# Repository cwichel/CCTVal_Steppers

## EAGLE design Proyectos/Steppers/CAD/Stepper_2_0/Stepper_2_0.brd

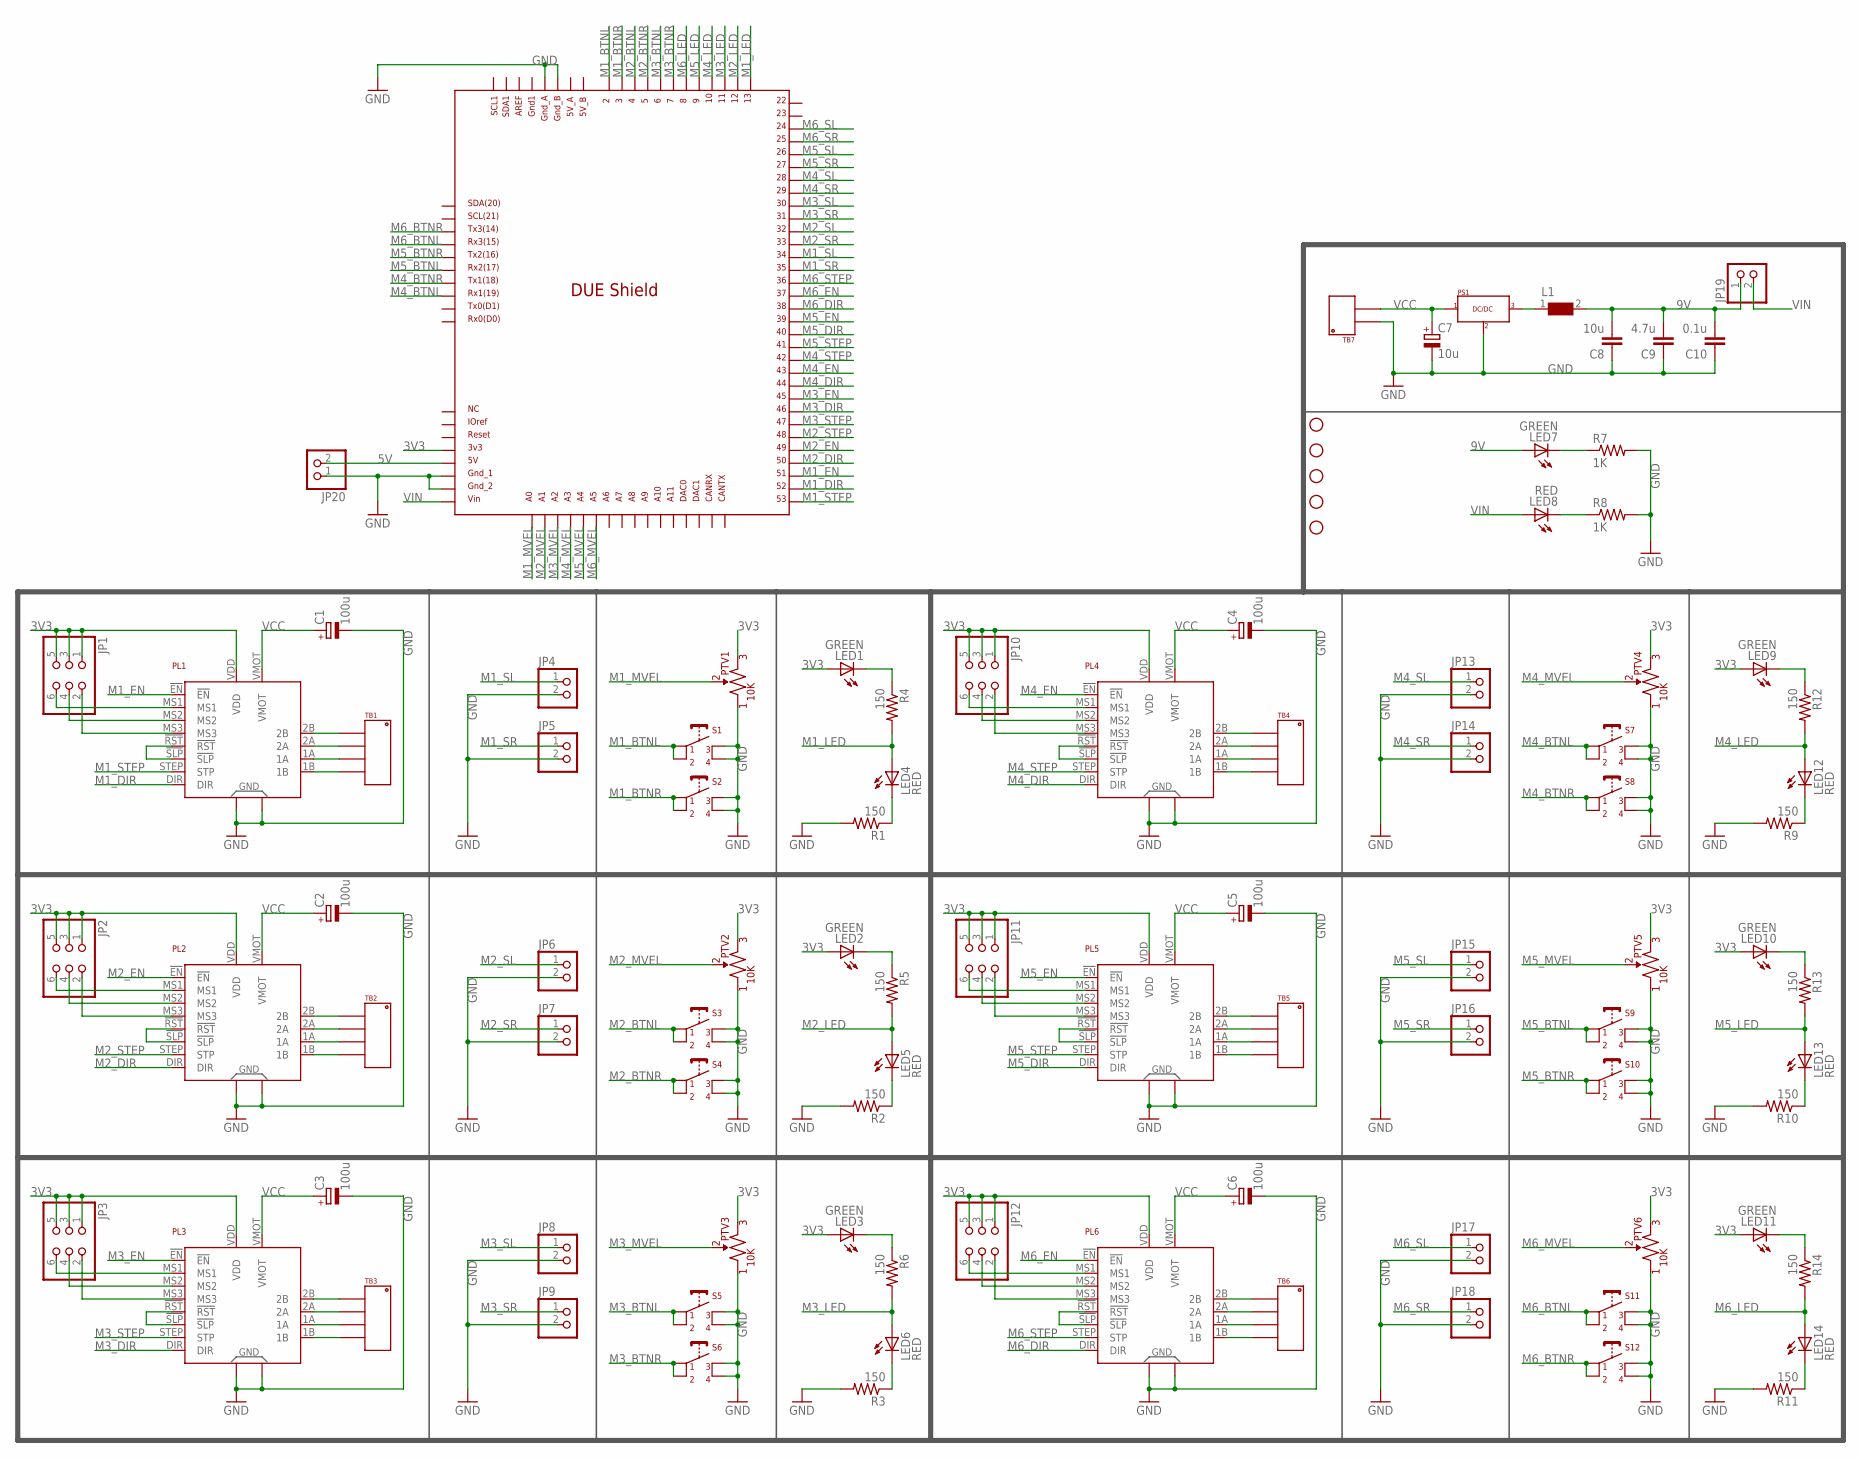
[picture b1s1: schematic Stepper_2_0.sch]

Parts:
C1, C2, C3, C4, C5, C6: 100u; ETR2
C7: 10u; E2-4
C8: 10u; 1206
C9: 4.7u; 1206
C10: 0.1u; 1206
DUE1: DUE(NOSPI)
H1, H2, H3, H4, H5: STAND-OFF
JP1, JP2, JP3, JP10, JP11, JP12: PINHD-2X3; 2X03
JP4, JP5, JP6, JP7, JP8, JP9, JP13, JP14, JP15, JP16, JP17, JP18, JP19, JP20: PINHD-1X2; 1X02
L1: WE-CBF-742792118_1206; 1206
LED1, LED2, LED3, LED7, LED9, LED10, LED11: GREEN; 1206
LED4, LED5, LED6, LED8, LED12, LED13, LED14: RED; 1206
PL1, PL2, PL3, PL4, PL5, PL6: A4988X; MD09X
PS1: VX78-500
PTV1, PTV2, PTV3, PTV4, PTV5, PTV6: 10K; PTV09A-4
R1, R2, R3, R4, R5, R6, R9, R10, R11, R12, R13, R14: 150; 1206
R7, R8: 1K; 1206
S1, S2, S3, S4, S5, S6, S7, S8, S9, S10, S11, S12: BTN_SPST_6MM
TB1, TB2, TB3, TB4, TB5, TB6: TB_HEAD_3.5MM_01X04
TB7: TB_HEAD_3.5MM_01X02

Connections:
3V3: DUE1.3V3, JP1.1, JP1.3, JP1.5, JP2.1, JP2.3, JP2.5, JP3.1, JP3.3, JP3.5, JP10.1, JP10.3, JP10.5, JP11.1, JP11.3, JP11.5, JP12.1, JP12.3, JP12.5, LED1.A, LED2.A, LED3.A, LED9.A, LED10.A, LED11.A, PL1.VDD, PL2.VDD, PL3.VDD, PL4.VDD, PL5.VDD, PL6.VDD, PTV1.P$3 (3), PTV2.P$3 (3), PTV3.P$3 (3), PTV4.P$3 (3), PTV5.P$3 (3), PTV6.P$3 (3)
5V: DUE1.5V, JP20.2
9V: C8.2, C9.2, C10.2, JP19.1, L1.2, LED7.A
GND: C1.-, C2.-, C3.-, C4.-, C5.-, C6.-, C7.-, C8.1, C9.1, C10.1, DUE1.GND_1, DUE1.GND_2, DUE1.GND_A, DUE1.GND_B, JP4.2, JP5.2, JP6.2, JP7.2, JP8.2, JP9.2, JP13.2, JP14.2, JP15.2, JP16.2, JP17.2, JP18.2, JP20.1, PL1.GND1, PL1.GND2, PL2.GND1, PL2.GND2, PL3.GND1, PL3.GND2, PL4.GND1, PL4.GND2, PL5.GND1, PL5.GND2, PL6.GND1, PL6.GND2, PS1.P$3, PTV1.P$1 (1), PTV2.P$1 (1), PTV3.P$1 (1), PTV4.P$1 (1), PTV5.P$1 (1), PTV6.P$1 (1), R1.2, R2.2, R3.2, R7.2, R8.2, R9.2, R10.2, R11.2, S1.P$3 (3), S1.P$4 (4), S2.P$3 (3), S2.P$4 (4), S3.P$3 (3), S3.P$4 (4), S4.P$3 (3), S4.P$4 (4), S5.P$3 (3), S5.P$4 (4), S6.P$3 (3), S6.P$4 (4), S7.P$3 (3), S7.P$4 (4), S8.P$3 (3), S8.P$4 (4), S9.P$3 (3), S9.P$4 (4), S10.P$3 (3), S10.P$4 (4), S11.P$3 (3), S11.P$4 (4), S12.P$3 (3), S12.P$4 (4), TB7.P$1
M1_BTNL: DUE1.2, S1.P$1 (1), S1.P$2 (2)
M1_BTNR: DUE1.3, S2.P$1 (1), S2.P$2 (2)
M1_DIR: DUE1.52, PL1.DIR
M1_EN: DUE1.51, PL1.!EN
M1_LED: DUE1.13, LED4.A, R4.2
M1_MVEL: DUE1.A0, PTV1.P$2 (2)
M1_SL: DUE1.34, JP4.1
M1_SR: DUE1.35, JP5.1
M1_STEP: DUE1.53, PL1.STEP (STP)
M2_BTNL: DUE1.4, S3.P$1 (1), S3.P$2 (2)
M2_BTNR: DUE1.5, S4.P$1 (1), S4.P$2 (2)
M2_DIR: DUE1.50, PL2.DIR
M2_EN: DUE1.49, PL2.!EN
M2_LED: DUE1.12, LED5.A, R5.2
M2_MVEL: DUE1.A1, PTV2.P$2 (2)
M2_SL: DUE1.32, JP6.1
M2_SR: DUE1.33, JP7.1
M2_STEP: DUE1.48, PL2.STEP (STP)
M3_BTNL: DUE1.6, S5.P$1 (1), S5.P$2 (2)
M3_BTNR: DUE1.7, S6.P$1 (1), S6.P$2 (2)
M3_DIR: DUE1.46, PL3.DIR
M3_EN: DUE1.45, PL3.!EN
M3_LED: DUE1.11, LED6.A, R6.2
M3_MVEL: DUE1.A2, PTV3.P$2 (2)
M3_SL: DUE1.30, JP8.1
M3_SR: DUE1.31, JP9.1
M3_STEP: DUE1.47, PL3.STEP (STP)
M4_BTNL: DUE1.RX1, S7.P$1 (1), S7.P$2 (2)
M4_BTNR: DUE1.TX1, S8.P$1 (1), S8.P$2 (2)
M4_DIR: DUE1.44, PL4.DIR
M4_EN: DUE1.43, PL4.!EN
M4_LED: DUE1.10, LED12.A, R12.2
M4_MVEL: DUE1.A3, PTV4.P$2 (2)
M4_SL: DUE1.28, JP13.1
M4_SR: DUE1.29, JP14.1
M4_STEP: DUE1.42, PL4.STEP (STP)
M5_BTNL: DUE1.RX2, S9.P$1 (1), S9.P$2 (2)
M5_BTNR: DUE1.TX2, S10.P$1 (1), S10.P$2 (2)
M5_DIR: DUE1.40, PL5.DIR
M5_EN: DUE1.39, PL5.!EN
M5_LED: DUE1.9, LED13.A, R13.2
M5_MVEL: DUE1.A4, PTV5.P$2 (2)
M5_SL: DUE1.26, JP15.1
M5_SR: DUE1.27, JP16.1
M5_STEP: DUE1.41, PL5.STEP (STP)
M6_BTNL: DUE1.RX3, S11.P$1 (1), S11.P$2 (2)
M6_BTNR: DUE1.TX3, S12.P$1 (1), S12.P$2 (2)
M6_DIR: DUE1.38, PL6.DIR
M6_EN: DUE1.37, PL6.!EN
M6_LED: DUE1.8, LED14.A, R14.2
M6_MVEL: DUE1.A5, PTV6.P$2 (2)
M6_SL: DUE1.24, JP17.1
M6_SR: DUE1.25, JP18.1
M6_STEP: DUE1.36, PL6.STEP (STP)
unnamed: PL2.1B, TB2.P$4
unnamed: PL2.1A, TB2.P$3
unnamed: PL2.2A, TB2.P$2
unnamed: PL2.2B, TB2.P$1
unnamed: PL2.!RST, PL2.!SLP
unnamed: JP2.2, PL2.MS3
unnamed: JP2.4, PL2.MS2
unnamed: JP2.6, PL2.MS1
unnamed: LED4.C, R1.1
unnamed: LED5.C, R2.1
unnamed: LED1.C, R4.1
unnamed: LED2.C, R5.1
unnamed: PL3.1B, TB3.P$4
unnamed: PL3.1A, TB3.P$3
unnamed: PL3.2A, TB3.P$2
unnamed: PL3.2B, TB3.P$1
unnamed: PL3.!RST, PL3.!SLP
unnamed: JP3.2, PL3.MS3
unnamed: JP3.4, PL3.MS2
unnamed: JP3.6, PL3.MS1
unnamed: LED6.C, R3.1
unnamed: LED3.C, R6.1
unnamed: PL4.1B, TB4.P$4
unnamed: PL4.1A, TB4.P$3
unnamed: PL4.2A, TB4.P$2
unnamed: PL4.2B, TB4.P$1
unnamed: PL4.!RST, PL4.!SLP
unnamed: JP10.2, PL4.MS3
unnamed: JP10.4, PL4.MS2
unnamed: JP10.6, PL4.MS1
unnamed: LED12.C, R9.1
unnamed: LED9.C, R12.1
unnamed: PL5.1B, TB5.P$4
unnamed: PL5.1A, TB5.P$3
unnamed: PL5.2A, TB5.P$2
unnamed: PL5.2B, TB5.P$1
unnamed: PL5.!RST, PL5.!SLP
unnamed: JP11.2, PL5.MS3
unnamed: JP11.4, PL5.MS2
unnamed: JP11.6, PL5.MS1
unnamed: LED13.C, R10.1
unnamed: LED10.C, R13.1
unnamed: PL6.1B, TB6.P$4
unnamed: PL6.1A, TB6.P$3
unnamed: PL6.2A, TB6.P$2
unnamed: PL6.2B, TB6.P$1
unnamed: PL6.!RST, PL6.!SLP
unnamed: JP12.6, PL6.MS1
unnamed: JP12.4, PL6.MS2
unnamed: JP12.2, PL6.MS3
unnamed: LED14.C, R11.1
unnamed: PL1.1B, TB1.P$4
unnamed: PL1.1A, TB1.P$3
unnamed: PL1.2A, TB1.P$2
unnamed: PL1.2B, TB1.P$1
unnamed: LED11.C, R14.1
unnamed: PL1.!RST, PL1.!SLP
unnamed: JP1.2, PL1.MS3
unnamed: JP1.4, PL1.MS2
unnamed: JP1.6, PL1.MS1
unnamed: L1.1, PS1.P$2
unnamed: LED7.C, R7.1
unnamed: LED8.C, R8.1
VCC: C1.+, C2.+, C3.+, C4.+, C5.+, C6.+, C7.+, PL1.VMOT, PL2.VMOT, PL3.VMOT, PL4.VMOT, PL5.VMOT, PL6.VMOT, PS1.P$1, TB7.P$2
VIN: DUE1.VIN, JP19.2, LED8.A

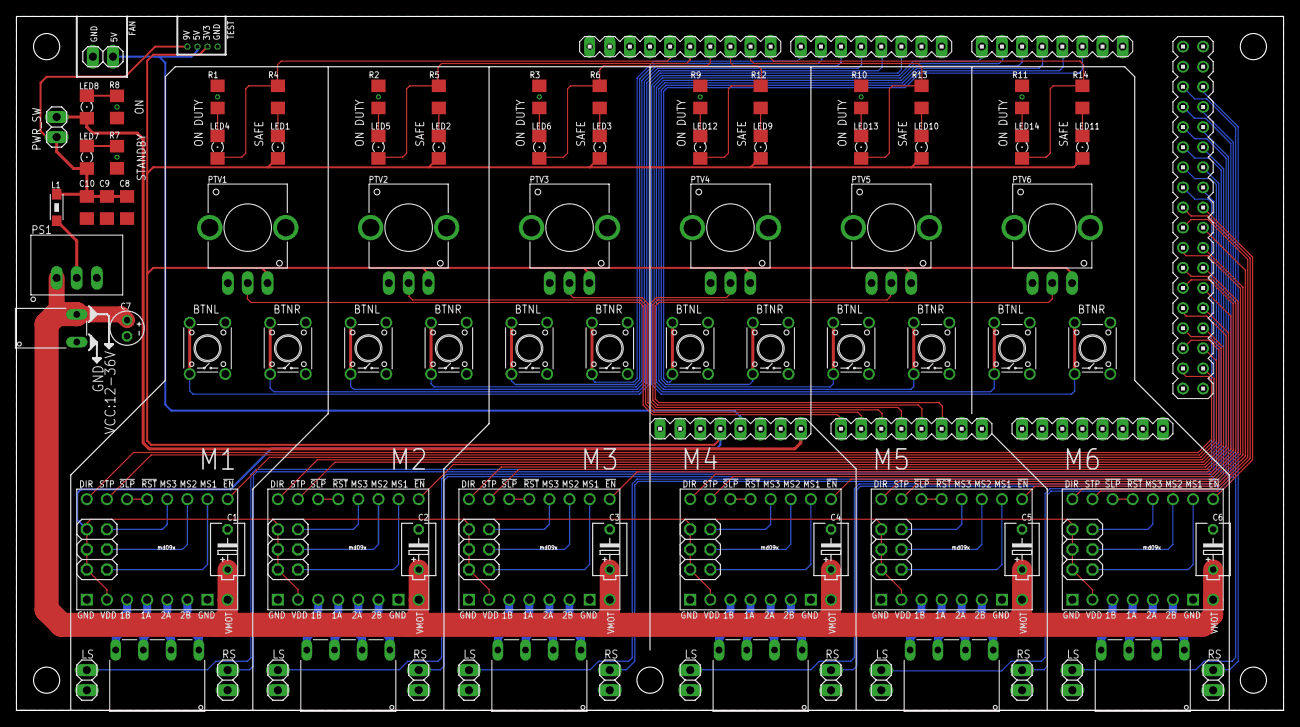
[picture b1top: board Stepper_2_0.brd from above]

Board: 2 copper layers, 160.0 x 87.6 mm, 97 parts (0 on the bottom side), 123 nets.

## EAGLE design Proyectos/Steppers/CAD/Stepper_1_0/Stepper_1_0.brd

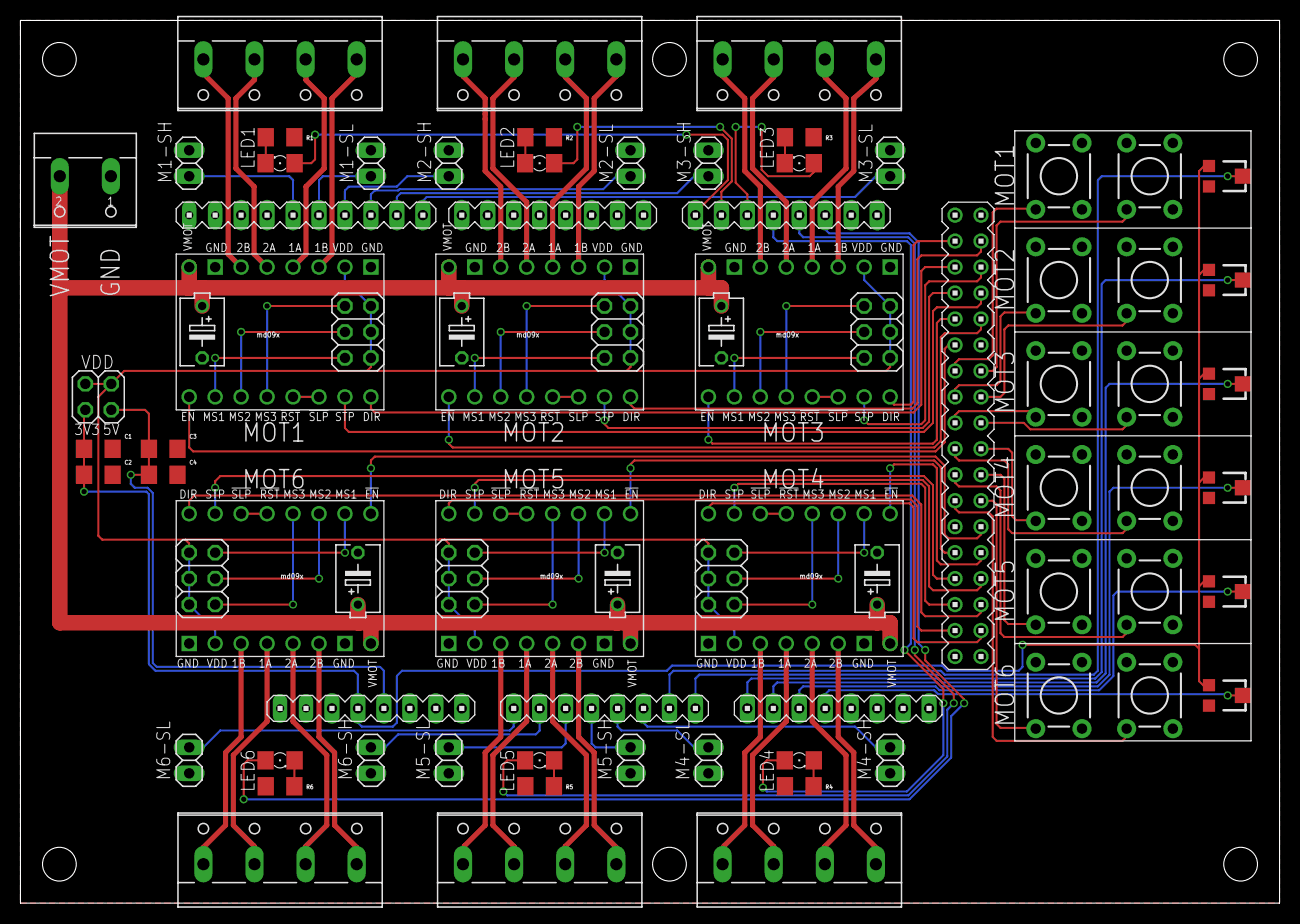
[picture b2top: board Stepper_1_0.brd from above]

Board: 2 copper layers, 123.2 x 86.4 mm, 79 parts (0 on the bottom side), 113 nets.

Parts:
C1, C3: 10u; 1206
C2, C4: 0.1u; 1206
C7, C8, C9, C10, C11, C12: 100u; ETR2
H1, H2, H3, H4, H5, H6: STAND-OFF
JP1, JP2, JP3, JP4, JP5, JP6, JP7, JP8, JP9, JP10, JP11, JP12: 1X02
JP13: 2X02
JP14, JP15, JP16, JP17, JP18, JP19: 2X03
LED1, LED2, LED3, LED4, LED5, LED6: 1206
PL1, PL2, PL3, PL4, PL5, PL6: A4988X; MD09X
R1, R2, R3, R4, R5, R6: 22; 1206
S1, S2, S3, S4, S5, S6, S7, S8, S9, S10, S11, S12: SWITCH-MOMENTARY-2PTH; TACTILE-PTH
SH1: DUE(NOSPI)
TM1, TM2, TM3, TM4, TM5, TM6: 10K; TC33X
X1: W237-102
X2, X3, X4, X5, X6, X7: W237-4

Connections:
3V3: C1.1, C2.1, JP13.1, SH1.3V3, TM1.1, TM2.1, TM3.1, TM4.1, TM5.1, TM6.1
5V: C3.1, C4.1, JP13.3, SH1.5V
GND: C1.2, C2.2, C3.2, C4.2, C7.-, C8.-, C9.-, C10.-, C11.-, C12.-, JP1.1, JP2.1, JP3.1, JP4.1, JP5.1, JP6.1, JP7.1, JP8.1, JP9.1, JP10.1, JP11.1, JP12.1, PL1.GND1, PL1.GND2, PL2.GND1, PL2.GND2, PL3.GND1, PL3.GND2, PL4.GND1, PL4.GND2, PL5.GND1, PL5.GND2, PL6.GND1, PL6.GND2, R1.1, R2.1, R3.1, R4.1, R5.1, R6.1, S1.3, S2.3, S3.3, S4.3, S5.3, S6.3, S7.3, S8.3, S9.3, S10.3, S11.3, S12.3, SH1.GND1, SH1.GND_1, SH1.GND_2, SH1.GND_A, SH1.GND_B, TM1.3, TM2.3, TM3.3, TM4.3, TM5.3, TM6.3, X1.1
M1-1A: PL1.1A, X2.2
M1-1B: PL1.1B, X2.1
M1-2A: PL1.2A, X2.3
M1-2B: PL1.2B, X2.4
M1-AUX: SH1.A6, TM1.2
M1-BTNL: S1.1, SH1.32
M1-BTNR: S2.1, SH1.33
M1-DIR: PL1.DIR, SH1.24
M1-EN: PL1.!EN, SH1.30
M1-LED: LED1.A, SH1.TX3
M1-SH: JP2.2, SH1.13
M1-SL: JP1.2, SH1.12
M1-STEP: PL1.STEP, SH1.27
M2-1A: PL2.1A, X3.2
M2-1B: PL2.1B, X3.1
M2-2A: PL2.2A, X3.3
M2-2B: PL2.2B, X3.4
M2-AUX: SH1.A7, TM2.2
M2-BTNL: S3.1, SH1.34
M2-BTNR: S4.1, SH1.35
M2-DIR: PL2.DIR, SH1.23
M2-EN: PL2.!EN, SH1.29
M2-LED: LED2.A, SH1.RX3
M2-SH: JP4.2, SH1.11
M2-SL: JP3.2, SH1.10
M2-STEP: PL2.STEP, SH1.26
M3-1A: PL3.1A, X4.2
M3-1B: PL3.1B, X4.1
M3-2A: PL3.2A, X4.3
M3-2B: PL3.2B, X4.4
M3-AUX: SH1.A8, TM3.2
M3-BTNL: S5.1, SH1.36
M3-BTNR: S6.1, SH1.37
M3-DIR: PL3.DIR, SH1.22
M3-EN: PL3.!EN, SH1.28
M3-LED: LED3.A, SH1.TX2
M3-SH: JP6.2, SH1.9
M3-SL: JP5.2, SH1.8
M3-STEP: PL3.STEP, SH1.25
M4-1A: PL4.1A, X5.2
M4-1B: PL4.1B, X5.1
M4-2A: PL4.2A, X5.3
M4-2B: PL4.2B, X5.4
M4-AUX: SH1.A9, TM4.2
M4-BTNL: S7.1, SH1.39
M4-BTNR: S8.1, SH1.38
M4-DIR: PL4.DIR, SH1.53
M4-EN: PL4.!EN, SH1.47
M4-LED: LED4.A, SH1.RX2
M4-SH: JP8.2, SH1.A5
M4-SL: JP7.2, SH1.A4
M4-STEP: PL4.STEP, SH1.50
M5-1A: PL5.1A, X6.2
M5-1B: PL5.1B, X6.1
M5-2A: PL5.2A, X6.3
M5-2B: PL5.2B, X6.4
M5-AUX: SH1.A10, TM5.2
M5-BTNL: S9.1, SH1.41
M5-BTNR: S10.1, SH1.40
M5-DIR: PL5.DIR, SH1.52
M5-EN: PL5.!EN, SH1.46
M5-LED: LED5.A, SH1.TX1
M5-SH: JP10.2, SH1.A3
M5-SL: JP9.2, SH1.A2
M5-STEP: PL5.STEP, SH1.49
M6-1A: PL6.1A, X7.2
M6-1B: PL6.1B, X7.1
M6-2A: PL6.2A, X7.3
M6-2B: PL6.2B, X7.4
M6-AUX: SH1.A11, TM6.2
M6-BTNL: S11.1, SH1.43
M6-BTNR: S12.1, SH1.42
M6-DIR: PL6.DIR, SH1.51
M6-EN: PL6.!EN, SH1.45
M6-LED: LED6.A, SH1.RX1
M6-SH: JP12.2, SH1.A1
M6-SL: JP11.2, SH1.A0
M6-STEP: PL6.STEP, SH1.48
unnamed: JP15.2, PL2.MS1
unnamed: PL1.!RST, PL1.!SLP
unnamed: JP15.6, PL2.MS3
unnamed: JP15.4, PL2.MS2
unnamed: PL2.!RST, PL2.!SLP
unnamed: PL3.!RST, PL3.!SLP
unnamed: JP16.6, PL3.MS3
unnamed: JP16.4, PL3.MS2
unnamed: PL4.!RST, PL4.!SLP
unnamed: JP14.6, PL1.MS3
unnamed: JP14.4, PL1.MS2
unnamed: JP14.2, PL1.MS1
unnamed: JP16.2, PL3.MS1
unnamed: JP17.6, PL4.MS3
unnamed: JP17.4, PL4.MS2
unnamed: JP17.2, PL4.MS1
unnamed: JP18.6, PL5.MS3
unnamed: JP18.4, PL5.MS2
unnamed: JP18.2, PL5.MS1
unnamed: JP19.6, PL6.MS3
unnamed: JP19.4, PL6.MS2
unnamed: JP19.2, PL6.MS1
unnamed: PL5.!RST, PL5.!SLP
unnamed: PL6.!RST, PL6.!SLP
unnamed: LED1.C, R1.2
unnamed: LED2.C, R2.2
unnamed: LED3.C, R3.2
unnamed: LED4.C, R4.2
unnamed: LED5.C, R5.2
unnamed: LED6.C, R6.2
VDD: JP13.2, JP13.4, JP14.1, JP14.3, JP14.5, JP15.1, JP15.3, JP15.5, JP16.1, JP16.3, JP16.5, JP17.1, JP17.3, JP17.5, JP18.1, JP18.3, JP18.5, JP19.1, JP19.3, JP19.5, PL1.VDD, PL2.VDD, PL3.VDD, PL4.VDD, PL5.VDD, PL6.VDD
VMM: C7.+, C8.+, C9.+, C10.+, C11.+, C12.+, PL1.VMOT, PL2.VMOT, PL3.VMOT, PL4.VMOT, PL5.VMOT, PL6.VMOT, X1.2

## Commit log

2017-09-13 Inicial
    Se agrega el trabajo actual al repositorio.
2017-09-14 Steppers:
    Se agregan nuevos componentes en la librería del proyecto, se comienza con el diseño esquemático de la versión 2
2017-09-14 Steppers:
    Se comienza a agregar el potenciómetro a lalibreria del proyecto, se avanza con el esquemático dela V2
2017-09-15 Steppers:
    Se mejora el modelo del potenciómetro en la libreria y se agrega l boton de 6mm, se avanza en el esquemático de la V2
2017-09-17 Steppers:
    Se avanza en el diseño esquemático y de PCB
2017-09-17 Steppers:
    Corrección de esquemático
2017-09-17 Steppers:
    Avance en PCB final, asignación de pines DUE.
2017-09-17 Steppers:
    Se finaliza el esquemático y PCB de forma funcional.
2017-09-17 Steppers:
    Se añaden pads para testeo de voltajes y conexión de 5V para ventilador.
2017-09-20 Steppers:
    Eagle proyect update
2017-09-22 Steppers:
    Se agregan las medidas de la placa para referencia.
2017-09-22 Steppers:
    BOM y Gerber
2017-09-26 Steppers:
    Se actualiza el BOM de compras en aliexpress
2017-09-26 Summary:
    Crear listas de compra para revisión.
2018-04-17 Update:
    - Nueva organización del proyecto
    - Inicio de modificaciones en el firmware

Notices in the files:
parts and their libraries:
SparkFun-Resistors: Licensing: Creative Commons ShareAlike 4.0 International - https://creativecommons.org/licenses/by-sa/4.0
